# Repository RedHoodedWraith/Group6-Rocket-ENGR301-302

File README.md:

# Group 6's Rocket Project
## Introduction
This project was developed as part of an in-class group project to design and develop a hobbyist rocket that used on-board programmable electronics to control it and to collect and report on-board telemetry.</br>
It was developed in 2020 by students in Group 6 from the [ENGR301](https://www.wgtn.ac.nz/courses/engr/301/2020) & [ENGR302](https://www.wgtn.ac.nz/courses/engr/302/2020) courses at the Victoria University of Wellington in New Zealand. 

While the students who worked on this project passed the aforementioned courses, at the time of writing, this project is in an unfinished state and there is not functioning rocket.</br>
The courses, ENGR301 & ENGR302, were focused on developing our skills around working on technical projects as part of a development team that uses Agile Development Practices. In the context of the courses above, this project was worked on to put into practice what we had learnt and to demonstrate our skills relating to using Agile.

While this project is incomplete and isn't likely to be worked on, anyone is welcome to use what we have made so far and/or to finish it off.

## Contributors

### Software
* Asami De Almeida
* Ketaki Bagal
* Penny Peneuta

### Hardware
* Jason McCormick
* Sean Osborne-Curtis
* Robert Reid
* Dylan Sukha

### University Staff Involved
* Andre Geldenhuis
* Aaron Chen

## Modules:

### Software Development
* Sun Incinerator Rocket Controller | PID system
* Sensor Test Programs
    * MPLI2C | Barometer + temperature readings.
    * MPU | | Gyro + Acceleartion readings, IMU+Servo Control.

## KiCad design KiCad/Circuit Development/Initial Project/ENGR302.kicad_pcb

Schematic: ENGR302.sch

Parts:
AE1: Antenna; PinHeader_1x01_P2.54mm_Vertical
BT1: 7.4V; PinHeader_1x02_P2.54mm_Vertical
BT2: 3.7V; PinHeader_1x02_P2.54mm_Vertical
C1: C; C_Axial_L3.8mm_D2.6mm_P10.00mm_Horizontal
C2: CP1; C_Axial_L3.8mm_D2.6mm_P10.00mm_Horizontal
C3, C5, C6, C7, C8, C10: CP1_Small; CP_Radial_D4.0mm_P2.00mm
C4, C9: CP1_Small; C_Axial_L3.8mm_D2.6mm_P7.50mm_Horizontal
D1: DIODE; Diode_DO-35_P10mm
J1: Conn_02x01; PinHeader_1x02_P2.54mm_Vertical
M1, M2: Motor_Servo; PinHeader_1x03_P2.54mm_Vertical
Q1: 2N7000; PinHeader_1x03_P2.54mm_Vertical
R1, R2, R3: R; R_Axial_DIN0204_L3.6mm_D1.6mm_P7.62mm_Horizontal
RV1: R_POT_TRIM; PinHeader_1x03_P2.54mm_Vertical
R_pulldown1: 10k-100k; R_Axial_DIN0204_L3.6mm_D1.6mm_P7.62mm_Horizontal
SafetySwitch1: SW_SPST; PinHeader_1x02_P2.54mm_Vertical
Super_C1: C; C_Axial_L5.1mm_D3.1mm_P10.00mm_Horizontal
TX1: RFM98W-433S2; XCVR_RFM98W-433S2
U1: MPU-6050-Board; MPU_6050_Board
U2: MPL3115a2_Board; mpl3115a2
U3: Adafruit-STM32F405; Adafruit_Feather
U4: GPS_Connector; PinHeader_1x04_P2.54mm_Vertical
U5: LM317_3PinPackage; PinHeader_1x03_P2.54mm_Vertical

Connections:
3.7_Battery: BT2.1 (+), C3.1, C8.1, U3.28 (Bat)
7.4: BT1.1 (+), C1.1, C5.1, SafetySwitch1.1 (A), U5.3 (VI)
Control: Q1.2 (G), R_pulldown1.1, U3.5 (A0)
Feather_Pin_Sensor: R2.1, U3.6 (A1)
GND: BT1.2 (-), BT2.2 (-), C1.2, C2.2, C3.2, C4.2, C5.2, C6.2, C7.2, C8.2, C9.2, C10.2, M1.3 (-), M2.3 (-), Q1.1 (S), R3.2, RV1.1, RV1.3, R_pulldown1.2, Super_C1.2, TX1.1 (GND), TX1.8 (GND), TX1.10 (GND), U1.3 (GND), U1.7 (GND), U2.2 (GND), U3.4 (GND), U4.1 (GND), U5.1 (ADJ)
unnamed: AE1.1, TX1.9 (ANT)
unnamed: C4.1, C6.1, C7.1, C10.1, TX1.13 (3.3V), U1.1 (VIN), U2.1 (Vin), U3.2 (3.3V), U3.3 (3.3V), U4.2 (Tx)
unnamed: D1.1 (K), SafetySwitch1.2 (B), Super_C1.1
unnamed: D1.2 (A), J1.1, R2.2, R3.1
unnamed: J1.2, Q1.3 (D)
unnamed: M1.1 (PWM), U3.21 (9)
unnamed: M2.1 (PWM), U3.20 (6)
unnamed: R1.2, RV1.2
unnamed: TX1.2 (MISO), U3.13 (MI)
unnamed: TX1.3 (MOSI), U3.12 (MU)
unnamed: TX1.4 (SCK), U3.11 (SCK)
unnamed: TX1.5 (NSS), U3.8 (A3)
unnamed: TX1.6 (RESET), U3.7 (A2)
unnamed: TX1.14 (DIO0), U3.23 (11)
unnamed: TX1.15 (DIO1), U3.22 (10)
unnamed: U1.4 (SCL), U2.6 (SCL), U3.18 (SCL)
unnamed: U1.6 (INT), U3.19 (5)
unnamed: U2.7 (SDA), U3.17 (SDA)
unnamed: U3.14 (RX), U4.4 (Vcc)
unnamed: U3.15 (TX), U4.3 (Rx)
~6V_Source: C2.1, C9.1, M1.2 (+), M2.2 (+), R1.1, U5.2 (VO)

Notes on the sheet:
Avionics package system Design
Contributors: Robert Reid, Dylan Sukha

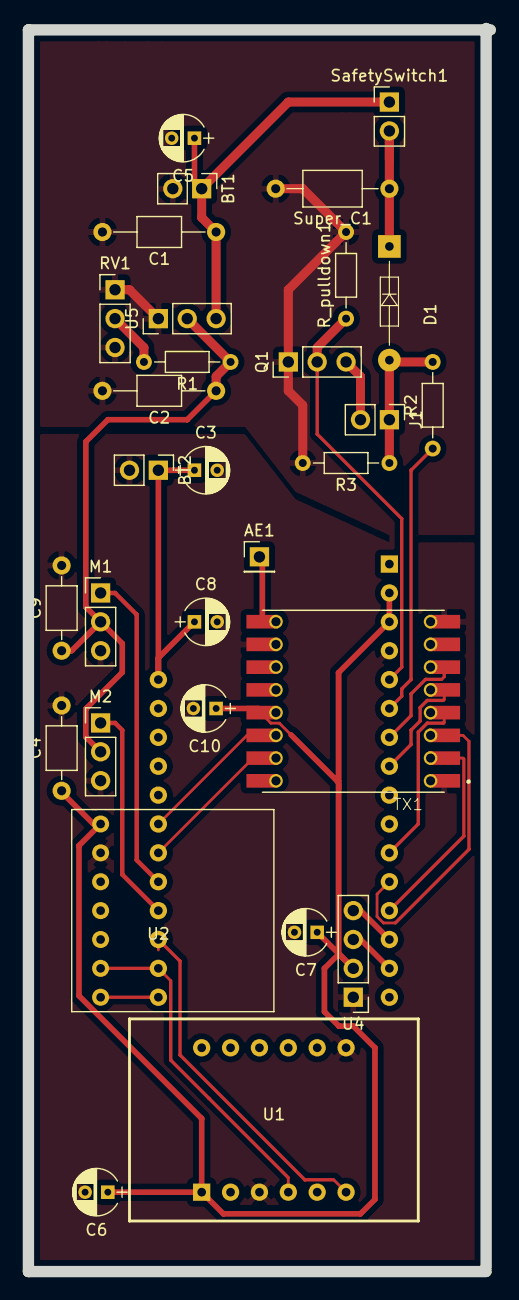
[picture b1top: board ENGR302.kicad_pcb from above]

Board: 2 copper layers, 40.6 x 109.3 mm, 31 parts (1 on the bottom side), 26 nets.

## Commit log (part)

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2020-05-07 Basic description of the hardware and software components of the avionics package
2020-05-07 The communication between the avionics package and other components of the system: mission control, rocket simulation
2020-05-07 Resolved review by Robert.
2020-05-07 Outlining 3.5 and allocating layout.
2020-05-07 Just some initial references, more to add
2020-05-08 Fixed some issues with what I wrote
2020-05-08 Basic definition of usability in the context of this particular system including brief paragraph on effectiveness and efficiency
2020-05-10 Added Recommended Improvements
    Added recommended improvements made by Penny.
2020-05-10 Added to non-UML parts.
2020-05-13 done section 3.9
2020-05-14 4.1 verification
2020-05-14 3.6 one para missing
2020-05-15 4.4 Performance requirements Verification
2020-05-15 Additions made regarding the usability requirements of the hardware component
2020-05-16 Wrote a bulk of 4.2.
2020-05-16 Fixed a few spotted errors.
2020-05-16 Added a paragraph on the ideal programming language that should be used in order to improve adaptability in the future
2020-05-17 Addition to first paragraph, mentioning the importance of building a strong avionics package that can withstand external factors
2020-05-17 draft
2020-05-19 1.3.3 fedback update
2020-05-19 Schedule - all dates to be confirmed
2020-05-19 Attempting to fix markdown
    The markdown didn't appear as I expected it to. This commit is just to test whether four spaces delivers the expected appearance.
2020-05-19 Added an extra new line between attributes
    This is to improve the markup.
2020-05-19 Test Markup
    I am going to try making the nested list points ordered instead of unordered. The problem I am trying to solve is the nested list keeps appearing closer to the next primary element (the attribute tit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
2020-05-19 Reverting Back
    That experiment didn't work as intended. I am reverting back to a nested unordered list
2020-05-20 Sprint method included
2020-05-20 Set up risks table
2020-05-21 Additions made that verify the adaptability of the rocket hardware when modifications are required
2020-05-21 Small sentence change to line 275
2020-05-21 Missing a space, otherwise all good.
2020-05-22 4.6 done
2020-05-22 Fixes according to Penny, typos and the like.
2020-05-22 Fixed Spelling Mistakes
    Fixed Spelling Mistakes in other people's work, including correcting the word "its" in line 49
2020-05-31 Prototype UML.
2020-06-06 Wrote 4.5 DMR.
2020-06-10 Added single line describing the need for a safety plan
    The safety plan will be placed into a separate document but referenced in this section. It will be developed according to the weeks planned ahead. A draft will be constructed and discussed with our s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
2020-06-10 Finishing Contribution Section
2020-06-11 client and purpose
2020-06-16 Fixed typo.
2020-06-18 Update Initial Parts List
2020-06-18 Update InitialPartsList
2020-06-18 Software Resources go here
2020-06-18 Adding jpg Block Diagram for Rocket System
2020-06-18 Added Software Prototype Project
    Created blank template for the project
2020-06-18 Started Rocket PID Prototype
    I'm trying this again
2020-06-18 Added Minor Updates to the PID Controller
    Currently, I'm working out the kinks to the PID controller
2020-06-18 Added Derivative
2020-06-18 Added to the table for the local council as well as a brief description of the NZSSA and their connection to the rocket project, specifically the avionics package and rocket
2020-06-18 Added More Content to the PID
    Added more content to the PID prototype. I am now trying to fine tune it.
2020-06-19 table update
2020-06-19 Added Fail Safe for Buffer Overflows when adding to the Integral Value
    Following Jolon's recommendations, I added that fail-safe recommendation to ensure if a buffer overflow occurs, the maximum possible value is used to store the integral value.
2020-06-19 Added a Negative Zero Comparator and Added Comments
    Added a function that checks if two values are equal, accounting for negative zero float values. Negative zero float values are treated as zero.
    Added additional comments for clarification.
2020-07-01 Dialogue Retrospective Sheet for the first Semester, during this we reflected on our methods throughout the previous 12 weeks and what we will do differently.
2020-07-17 New commit tracker for hardware development.
2020-07-20 Servo adapter, using smaller servo which does not fit with the original Gimbal Design, so adapter to account for size difference
2020-07-20 Pitch Component of Gimbal
2020-07-20 Motor Case Component of Gimbal
2020-07-21 Other part of the servo adapter, final design
2020-07-22 LoRa Example Code
2020-07-22 Adding block diagram jpg for @rathodrowa software system
2020-07-23 Added the Dockerfile to the correct branch
2020-07-24 Something changed. Don't know what though
2020-07-26 Replace Rocket_Block_Diagram.jpg
2020-07-26 Added all ordered parts (up to 2nd wave).
2020-07-26 Updates to the Dockerfile and .yml configuration
2020-07-26 Added code to List current directory
2020-07-26 Added a message
    This is to help me develop
2020-07-26 Build Docker Image?
2020-07-26 Fixed File Path to turn into an executable
2020-07-26 Returned the Dockerfile back to Apline
    Tried using Linux, didn't go so well and it seems heavy. Switching back to Apline. This time I am adjusting the file to install dependencies using the Alpine APK instead of Debian's apt-get
2020-07-26 Removed --q flag
2020-07-26 Switching back to Ubuntu
    Turns out many of the resources needed by PlatformIO is better run on Ubuntu
2020-07-26 Minor adjustments
    Added the -y flag for apt-get and switched one use of pip to pip3
2020-07-26 Changed Software Runner to a Python File
2020-07-26 Minor Syntax Change
2020-07-26 Trying Python script with exit code 1
2020-07-26 Configured this one to pass
    The previous one was configured to fail. I have configured this one to pass.
2020-07-26 Switching the Build Process to the Docker Runner
2020-07-26 Added "ls" to help me diagnose where the Docker image is running
2020-07-26 Trying this without a script
2020-07-26 Trying GitLab Runner
2020-07-26 Trying This
    This is rather frustrating if I'll be honest.
2020-07-26 ..... I don't even know....
2020-07-26 Reverting back to this
    I am reverting back to what I definitely know works
2020-07-26 How about this?
2020-07-26 Added a tag to the dockerfile builder
2020-07-26 Started Pipeline for KiCad Verification
2020-07-26 Corrected apk tag
2020-07-27 Dialogue sheet results
2020-07-27 Clean up file
2020-07-27 Padparadcha Communications
    Created empty library for the Padparadcha (Communications) package
2020-07-27 Created basic skeleton code for rhodonite (external sensors)
2020-07-27 Servo manual to determine duty cycles and voltages for operations
2020-07-27 Opened the Workspace in CLion
    This workspace is now openable via CLion that has the PlatformIO add-on added
2020-07-27 Added Documentation for Software Folder
    Added documentation explaining how to add a PlatformIO workspace to be tested for a successful compile as part of the Pipeline job for this repository.
2020-07-27 Corrected the spelling of Padparadscha
2020-07-27 Skeleton Code for Padparadscha & Added 'Lars' package for Common Header
    I have added some template code for the Padparadscha (Communications) package and added a 'Lars' header file to include common libraries.
2020-07-28 Added constructor and a few variables into the rhodonite code as a start The variables so far only cover part of the sensors, particularly the GPS ans barometer. These are subject to be being changed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
2020-07-29 Added Minor Content to Rutile (Servo Controller)
2020-08-03 Adding a variable for IMU to the rhodonite code
2020-08-03 added constructor, variables, getters and setters
2020-08-03 Fixing syntax error
2020-08-03 Testing changes
2020-08-03 small error fixed
2020-08-04 Moving file into directory
2020-08-06 Library file for Adafruit file
2020-08-06 Upload New Files
2020-08-06 Adding final mailmap changes after testing to see if it works
2020-08-06 Update Hardware Work Flow/Voltage Regulator Design
2020-08-07 Initialise Peer Matrix
2020-08-09 Added Sample File to update folder name
    Long story short, I've updated the folder name from "software" to "Software" however I'm trying to get GitLab to synchronise those changes.
2020-08-09 Updated the Dockerfile to reflect folder name change
2020-08-09 Temporary Renamed Software Folder
    Temporarily renamed "software" folder to "Software1" so I can then change it to "Software" with a capital 'S' after this commit. This is to force Git into renaming the folder
2020-08-09 Changed the file name for README
    Removed the file extension for the README in the 'Sun_Incinerator_Rocket_Controller' folder
2020-08-10 Removed Duplicate Library
    Somehow we ended up with 2 Rutile (Servo) libraries. I removed the empty duplicate.
2020-08-12 Upload updated Retrospective 3 file
2020-08-14 Added an Error Handling object
    This object can be used to report errors via the Serial Port
2020-08-14 WIP: Changed the Error Handler to Diagnostic Handler
    Work in progress and will not build yet. I have changed the Error Handler to a Diagnostic Handler and added a feature where a message can be reported as well as an error.
    Currently stuck on the Padparadscha object not being passed through the constructor.
2020-08-14 Successfully Separated the Serial Handling Class
    Now each object requires a PadparadschaSerial object instead of the whole Padparadscha (communications) class object.
    The Padparadscha class creates and contains a PadparadschaSerial object within it.
2020-08-14 Implemented a function that returns a P'aSerial Object Pointer
    P'a = Padparadscha
2020-09-01 Update Hardware Work Flow/Investigation of PWM Interrupts
2020-09-02 Created a Separate Project to test out the LoRa code
2020-09-02 Literally One Line Changed
    That's it. I don't know why this wasn't included in the previous commit.
2020-09-04 Started connections
2020-09-07 Organising components and adding connections
2020-09-08 Wiring of breadboard
2020-09-08 Update Breadboard Wiring Image
2020-09-09 Tested the Hello World Project
    Currently it works on an Arduino Uno but not for the STM32. I am not sure what is happening
2020-09-11 Created a Test Serial Project
2020-09-14 Started Sample Program
    This is an example program to test the LoRa Communications
2020-09-14 adding basestation RX and incl labels
2020-09-23 Design and Include Ignition Circuit for Parachute
2020-09-23 Small changes
2020-09-28 Sample Code for Writing to a MicroSD Card
2020-09-28 Added Upload Protocol to DFU
2020-09-30 Moved MicroSD Card Code to Sample Software
2020-09-30 Functioning SD Card Writer
2020-09-30 Added Group 13's CSV Standard
    This is documentation to help us format what to send to Mission Control via LoRa and what to write to the local micro-SD Card
2020-10-06 Finalising pin layout and assigning pins
2020-10-06 Added Communication Protocol Document
    Added information to help us format the CSV files.
2020-10-07 Made Some Dependency Improvements
    Code still doesn't build however we are getting better error messages this time.
2020-10-07 PCB Design
2020-10-07 Include PCB File
2020-10-12 Implementing size changes of board and track sizes
2020-10-13 Uploaded the sample programs.
    MPL readings and IMU-Servo controls.
2020-10-15 Prepared for handover.
2020-10-19 Distribution of Docs Organised
2020-10-19 Update software_dockerfile to reflect new folder name
2020-10-19 Added MIT License for the Software and Hardware Design Resources
2025-03-19 Updated Module Headers in README
2025-03-19 Updated README & Refactored Mentions of a Contributor to their current name
2025-03-19 Update README.md
    Changed Headers
